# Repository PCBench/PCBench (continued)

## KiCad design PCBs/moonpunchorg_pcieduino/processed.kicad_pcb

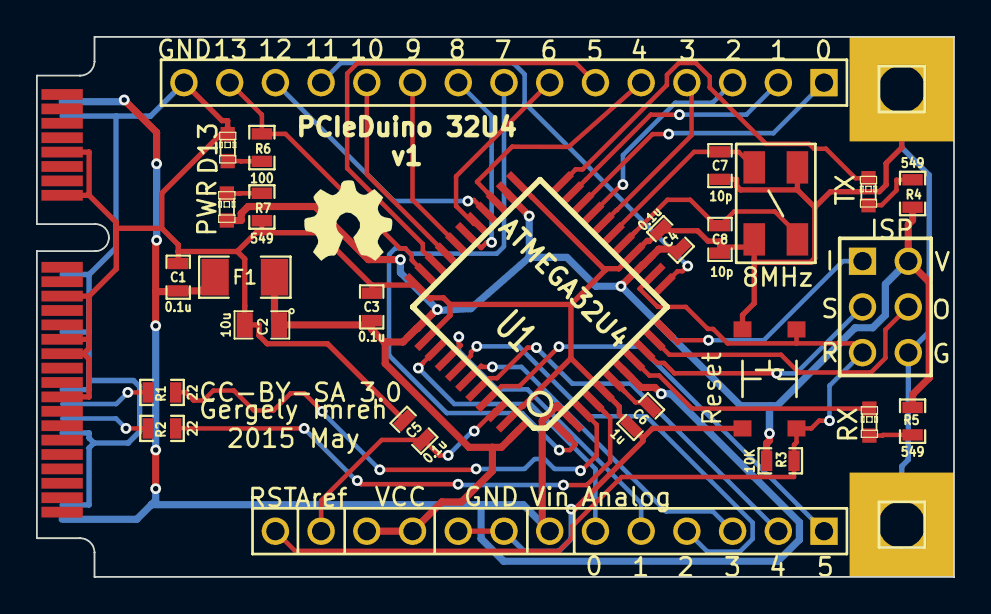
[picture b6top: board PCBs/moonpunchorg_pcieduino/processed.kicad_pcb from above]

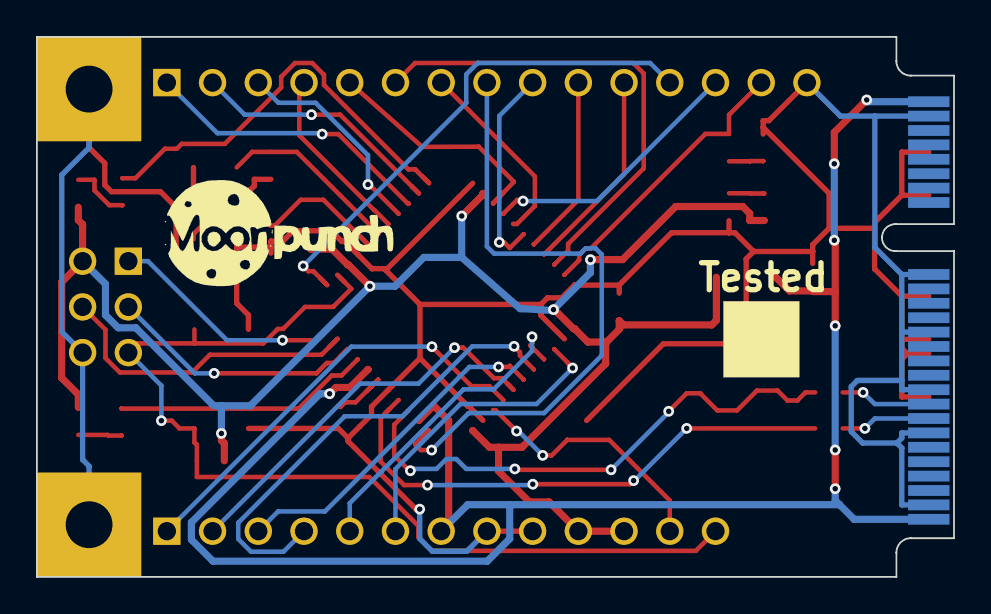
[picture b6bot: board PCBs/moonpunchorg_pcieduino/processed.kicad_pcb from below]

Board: 2 copper layers, 51.0 x 30.0 mm, 32 parts (2 on the bottom side), 41 nets.

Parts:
C1, C3, C4, C5: 0.1u; SM0603_Capa
C2: 10u; SM0805
C6: 1u; SM0603_Capa
C7, C8: 10p; SM0603_Capa
D1: TX; LED-0603
D2: RX; LED-0603
D3: D13; LED-0603
D4: PWR; LED-0603
F1: FUSE; SM1206
J1: PCIE-MINI; miniPCIeConn
J2: ISP; pin_array_3x2
J3: DIGITAL; PIN_ARRAY_15x1
J4: ANALOG_POWER; PIN_ARRAY_13x1
MOONPUNCH: LOGO
MOUNTING_HOLE1, MOUNTING_HOLE2: CONN_1; PIN_ARRAY_1
OSHW: LOGO; OSHW
R1, R2: 22; SM0603_Resistor
R3: 10K; SM0603_Resistor
R4, R5, R7: 549; SM0603_Resistor
R6: 100; SM0603_Resistor
SW1: Reset; SMD_SWITCH
TESTED: LOGO; SQUARE
U1: ATMEGA32U4; TQFP44
X1: 8MHz; SMDXTAL_50x32

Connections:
/A0: J4.6, U1.36
/A1: J4.5, U1.37
/A2: J4.4, U1.38
/A3: J4.3, U1.39
/A4: J4.2, U1.40
/A5: J4.1, U1.41
/AREF: C5.1, J4.12, U1.42
/D0/RXI: J3.1, U1.20
/D1/TXO: J3.2, U1.21
/D2/SDA: J3.3, U1.19
/D3/SCL: J3.4, U1.18
/D4: J3.5, U1.25
/D5: J3.6, U1.31
/D6: J3.7, U1.27
/D7: J3.8, U1.1
/D8: J3.9, U1.28
/D9: J3.10, U1.29
/D10: J3.11, U1.30
/D11: J3.12, U1.12
/D12: J3.13, U1.26
/D13: J3.14, R6.1, U1.32
/D+: R2.1, U1.4
/D-: R1.1, U1.3
/MISO: J2.1, U1.11
/MOSI: J2.4, U1.10
/RESET: J2.5, J4.13, R3.2, SW1.2, U1.13
/RXLED: D2.2, U1.8
/SCK: J2.3, U1.9
/TXLED: D1.2, U1.22
/UVCC: C1.1, F1.1, J1.2, J1.52, J4.7, U1.2, U1.7
GND: C1.2, C2.2, C3.2, C4.2, C5.2, C6.2, C7.2, C8.2, D3.2, J1.4, J1.9, J1.15, J1.18, J1.21, J1.26, J1.27, J1.29, J1.34, J1.35, J1.40, J1.50, J2.6, J3.15, J4.8, J4.9, MOUNTING_HOLE1.1, MOUNTING_HOLE2.1, R7.2, SW1.1, U1.5, U1.15, U1.23, U1.33, U1.35, U1.43, X1.3
unnamed: J1.36, R1.2
unnamed: J1.38, R2.2
unnamed: C6.1, U1.6
unnamed: D4.2, R7.1
unnamed: C8.1, U1.16, X1.2
unnamed: C7.1, U1.17, X1.1
unnamed: D3.1, R6.2
unnamed: D1.1, R4.1
unnamed: D2.1, R5.1
VCC: C2.1, C3.1, C4.1, D4.1, F1.2, J2.2, J4.10, J4.11, R3.1, R4.2, R5.2, U1.14, U1.24, U1.34, U1.44

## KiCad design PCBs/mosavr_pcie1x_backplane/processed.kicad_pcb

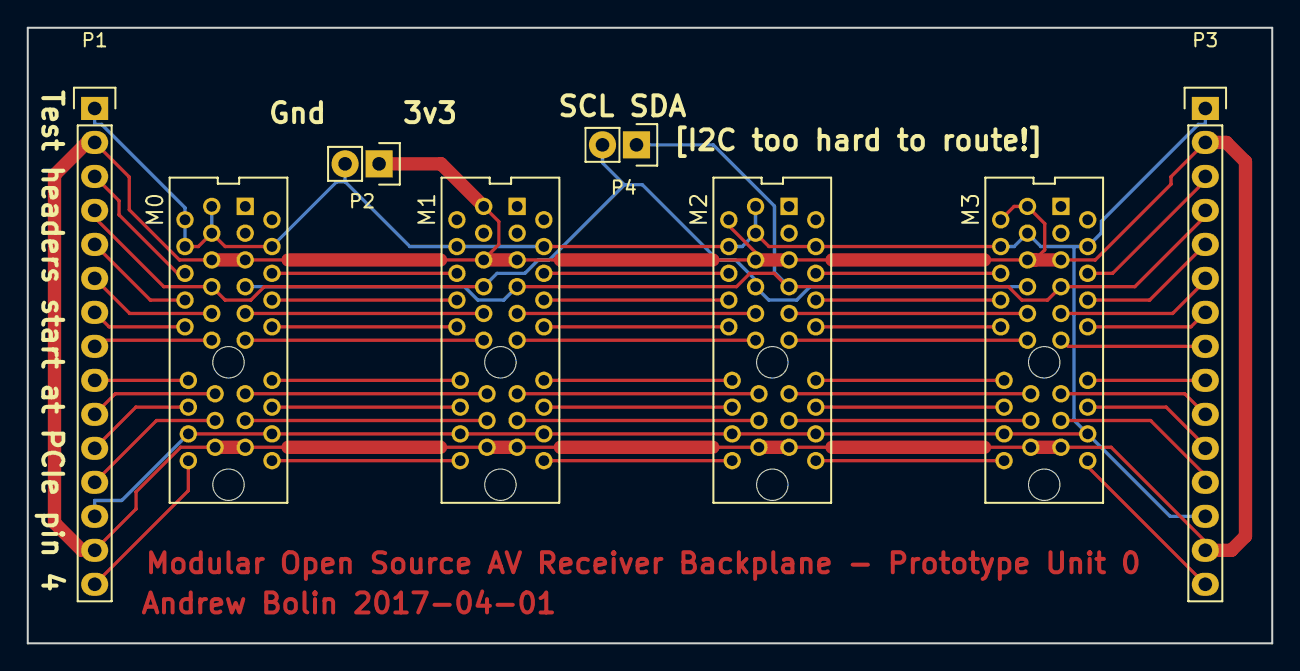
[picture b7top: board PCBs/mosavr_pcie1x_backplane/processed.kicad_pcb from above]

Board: 2 copper layers, 93.0 x 46.0 mm, 8 parts (0 on the bottom side), 54 nets.

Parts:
M0, M1, M2, M3: pcie_1x_conn; x1socket
P1, P3: CONN_01X15; Pin_Header_Straight_1x15
P2, P4: CONN_01X02; Pin_Header_Straight_1x02

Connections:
+3V3: M0.A5, M0.A17, M0.B5, M0.B17, M1.A5, M1.A17, M1.B1, M1.B5, M1.B17, M2.A5, M2.A17, M2.B2, M2.B5, M2.B17, M3.A5, M3.A17, M3.B1, M3.B2, M3.B5, M3.B17, P1.2, P1.14, P2.1, P3.2, P3.14
/SCL: M0.B7, M1.B7, M2.B7, M3.B7, P1.4, P4.2
/SDA: M0.A7, M1.A7, M2.A7, M3.A7, P3.4, P4.1
GND: M0.A4, M0.A16, M0.B1, M0.B2, M0.B3, M0.B4, M0.B16, M1.A4, M1.A16, M1.B4, M1.B16, M2.A4, M2.A16, M2.B1, M2.B3, M2.B4, M2.B16, M3.A4, M3.A16, M3.B3, M3.B4, M3.B16, P1.1, P1.13, P2.2, P3.1, P3.13
unnamed: M0.A6, M1.B6
unnamed: M0.A8, M1.B8
unnamed: M0.A9, M1.B9
unnamed: M0.A10, M1.B10
unnamed: M0.A11, M1.B11
unnamed: M0.A12, M1.B12
unnamed: M0.A13, M1.B13
unnamed: M0.A14, M1.B14
unnamed: M0.A15, M1.B15
unnamed: M0.A18, M1.B18
unnamed: M0.B6, P1.3
unnamed: M0.B8, P1.5
unnamed: M0.B9, P1.6
unnamed: M0.B10, P1.7
unnamed: M0.B11, P1.8
unnamed: M0.B12, P1.9
unnamed: M0.B13, P1.10
unnamed: M0.B14, P1.11
unnamed: M0.B15, P1.12
unnamed: M0.B18, P1.15
unnamed: M1.A6, M2.B6
unnamed: M1.A8, M2.B8
unnamed: M1.A9, M2.B9
unnamed: M1.A10, M2.B10
unnamed: M1.A11, M2.B11
unnamed: M1.A12, M2.B12
unnamed: M1.A13, M2.B13
unnamed: M1.A14, M2.B14
unnamed: M1.A15, M2.B15
unnamed: M1.A18, M2.B18
unnamed: M2.A6, M3.B6
unnamed: M2.A8, M3.B8
unnamed: M2.A9, M3.B9
unnamed: M2.A10, M3.B10
unnamed: M2.A11, M3.B11
unnamed: M2.A12, M3.B12
unnamed: M2.A13, M3.B13
unnamed: M2.A14, M3.B14
unnamed: M2.A15, M3.B15
unnamed: M2.A18, M3.B18
unnamed: M3.A6, P3.3
unnamed: M3.A8, P3.5
unnamed: M3.A9, P3.6
unnamed: M3.A10, P3.7
unnamed: M3.A11, P3.8
unnamed: M3.A12, P3.9
unnamed: M3.A13, P3.10
unnamed: M3.A14, P3.11
unnamed: M3.A15, P3.12
unnamed: M3.A18, P3.15
